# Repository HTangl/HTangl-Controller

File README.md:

# HTangl-Controller

The HTangl controller is an all digital game controller mainly made for Super Smash Brothers Melee  
but it can be used for many different games including traditional fighting games and platformers.  

It runs on a [modified version](https://github.com/HTangl/HTangl-Firmware) of the [HayB0XX firmware](https://github.com/JonnyHaystack/HayB0XX).  

The design of the controller is based on [The B0XX](https://b0xx.com/), [Frame 1](https://frame1.gg/) and [GCCMX](https://www.craneslab.xyz/projects/mx)  

This controller is not especially easy to DIY, Version 2 requiers a large 3D printed case which I print all in one piece on a large format FDM printer. The top panel and switch plate are also laser cut and the PCB requires some custom parts like the 2 USB ports. If you are not already somewhat familier with 3D printing, soldering, CAD and PCB manufacturing then I do not recommend trying to make one of these controllers.  

I created a simplified version of this controller specifically meant for DIY called the [BudgeTangl](https://github.com/HTangl/BudgeTangl), please check out that repository if you're just looking to make a simple controller.  

This controller is licensed under the CERN Open Hardware Licence Version 2 - Strongly Reciprocal. Please read the license in this repository and visit https://ohwr.org/cernohl for more information. This license allows you to make a modified or unmodified version of the controller for yourself or to sell provided you follow the guidelines of the license. The strongly reciprocal version of the license I have chosen requires that you use this same license if you decide to make modifications to any of the files in this repository.

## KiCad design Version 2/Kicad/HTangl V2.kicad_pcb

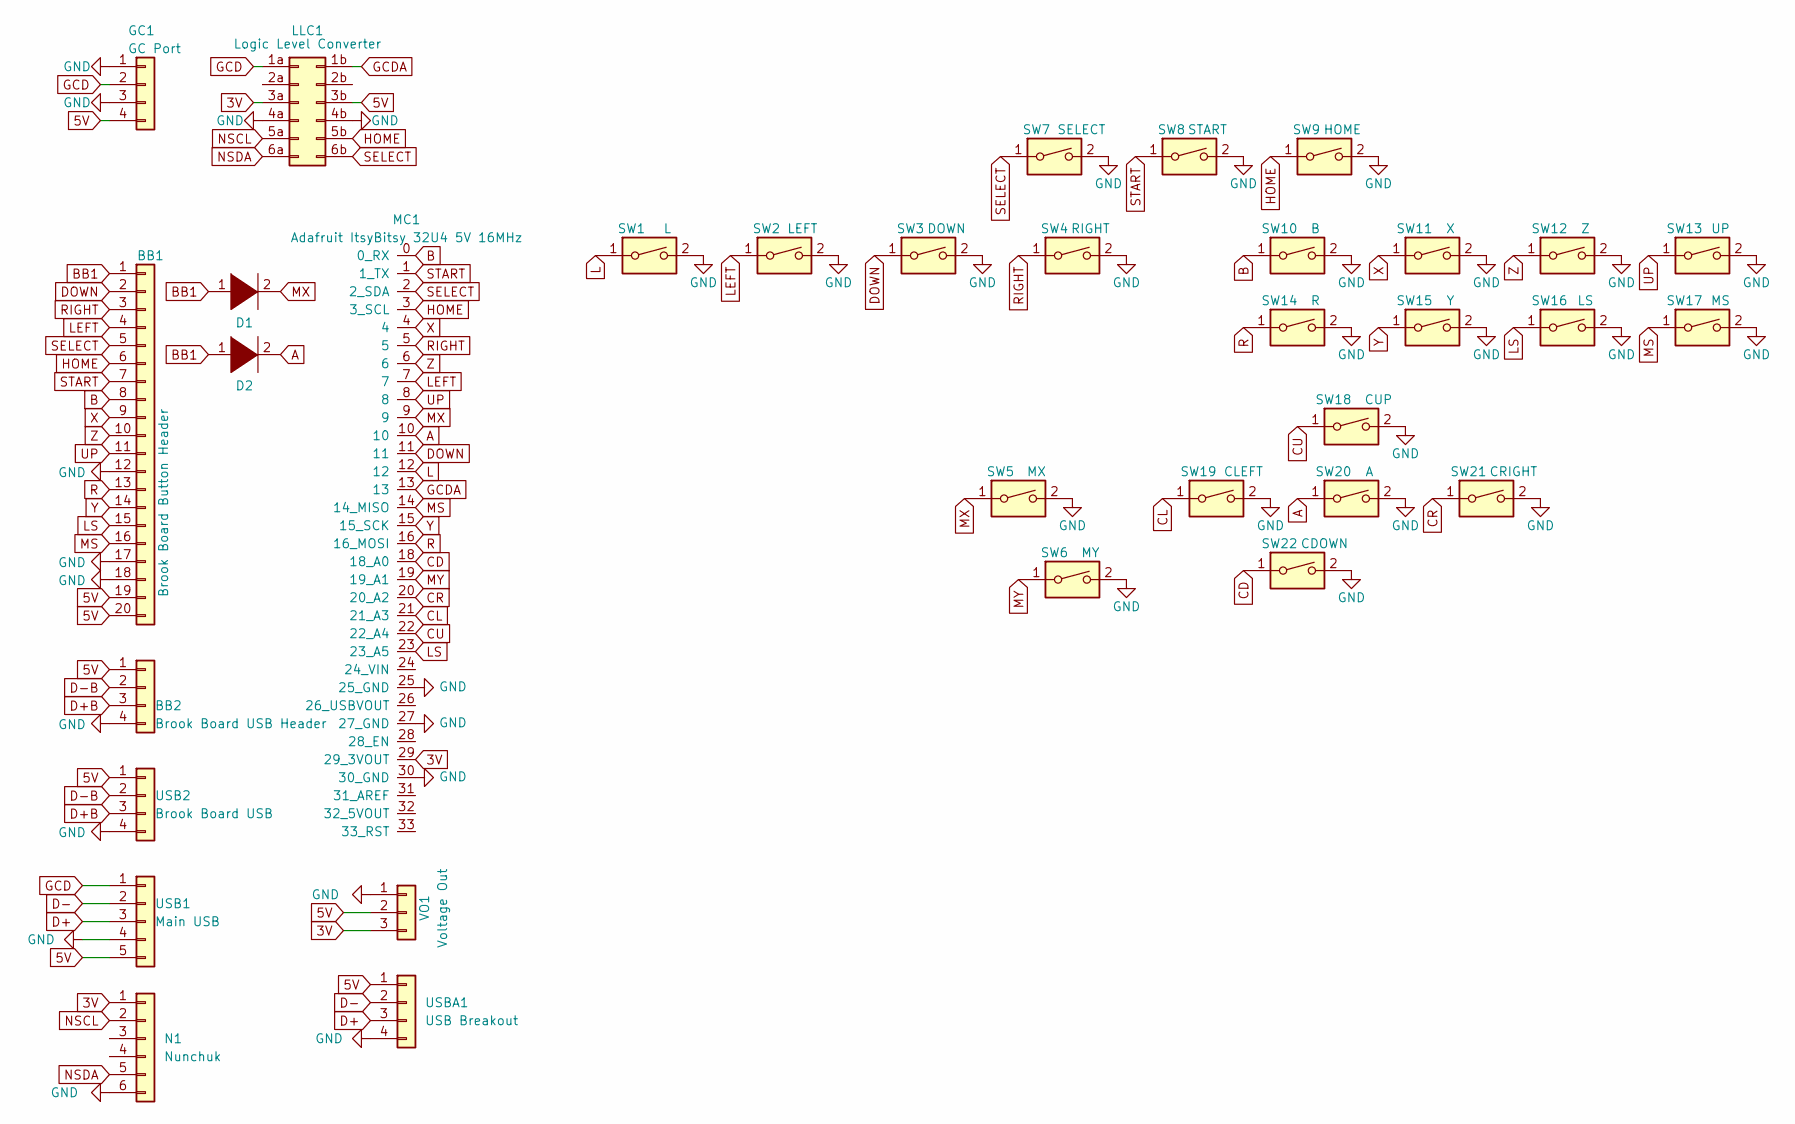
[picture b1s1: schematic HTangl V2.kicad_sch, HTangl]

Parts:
BB1: Brook Board Button Header; Brook_Board_Header_1
BB2: Brook Board USB Header; Brook_Board_Header_2
D1, D2: DIODE; D_DO-35_SOD27_P7.62mm_Horizontal
GC1: GC Port; PinSocket_1x04_P2.54mm_Vertical
LLC1: Logic Level Converter; LLC
MC1: Adafruit ItsyBitsy 32U4 5V 16MHz; Adafruit_32U4_5V
N1: Nunchuk; NunchuckFemale
SW1: L; Kailh_socket_MX_optional
SW2: LEFT; Kailh_socket_MX_optional
SW3: DOWN; Kailh_socket_MX_optional
SW4: RIGHT; Kailh_socket_MX_optional
SW5: MX; Kailh_socket_MX_optional
SW6: MY; Kailh_socket_MX_optional
SW7: SELECT; Kailh_socket_MX_optional
SW8: START; Kailh_socket_MX_optional
SW9: HOME; Kailh_socket_MX_optional
SW10: B; Kailh_socket_MX_optional
SW11: X; Kailh_socket_MX_optional
SW12: Z; Kailh_socket_MX_optional
SW13: UP; Kailh_socket_MX_optional
SW14: R; Kailh_socket_MX_optional
SW15: Y; Kailh_socket_MX_optional
SW16: LS; Kailh_socket_MX_optional
SW17: MS; Kailh_socket_MX_optional
SW18: CUP; Kailh_socket_MX_optional
SW19: CLEFT; Kailh_socket_MX_optional
SW20: A; Kailh_socket_MX_optional
SW21: CRIGHT; Kailh_socket_MX_optional
SW22: CDOWN; Kailh_socket_MX_optional
USB1: Main USB; Model_U_Header
USB2: Brook Board USB; Brook_Board_USBC
USBA1: USB Breakout; PinSocket_1x04_P2.54mm_Vertical
VO1: Voltage Out; PinHeader_1x03_P2.54mm_Vertical

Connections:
3V: LLC1.3a, MC1.29 (29_3VOUT), N1.1, VO1.3
5V: BB1.19, BB1.20, BB2.1, GC1.4, LLC1.3b, USB1.5, USB2.1, USBA1.1, VO1.2
A: D2.2 (A), MC1.10, SW20.1
B: BB1.8, MC1.0 (0_RX), SW10.1
BB1: BB1.1, D1.1 (K), D2.1 (K)
CD: MC1.18 (18_A0), SW22.1
CL: MC1.21 (21_A3), SW19.1
CR: MC1.20 (20_A2), SW21.1
CU: MC1.22 (22_A4), SW18.1
D+: USB1.3, USBA1.3
D+B: BB2.3, USB2.3
D-: USB1.2, USBA1.2
D-B: BB2.2, USB2.2
DOWN: BB1.2, MC1.11, SW3.1
GCD: GC1.2, LLC1.1a, USB1.1
GCDA: LLC1.1b, MC1.13
GND: BB1.12, BB1.17, BB1.18, BB2.4, GC1.1, GC1.3, LLC1.4a, LLC1.4b, MC1.25 (25_GND), MC1.27 (27_GND), MC1.30 (30_GND), N1.6, SW1.2, SW2.2, SW3.2, SW4.2, SW5.2, SW6.2, SW7.2, SW8.2, SW9.2, SW10.2, SW11.2, SW12.2, SW13.2, SW14.2, SW15.2, SW16.2, SW17.2, SW18.2, SW19.2, SW20.2, SW21.2, SW22.2, USB1.4, USB2.4, USBA1.4, VO1.1
HOME: BB1.6, LLC1.5b, MC1.3 (3_SCL), SW9.1
L: MC1.12, SW1.1
LEFT: BB1.4, MC1.7, SW2.1
LS: BB1.15, MC1.23 (23_A5), SW16.1
MS: BB1.16, MC1.14 (14_MISO), SW17.1
MX: D1.2 (A), MC1.9, SW5.1
MY: MC1.19 (19_A1), SW6.1
NSCL: LLC1.5a, N1.2
NSDA: LLC1.6a, N1.5
R: BB1.13, MC1.16 (16_MOSI), SW14.1
RIGHT: BB1.3, MC1.5, SW4.1
SELECT: BB1.5, LLC1.6b, MC1.2 (2_SDA), SW7.1
START: BB1.7, MC1.1 (1_TX), SW8.1
UP: BB1.11, MC1.8, SW13.1
X: BB1.9, MC1.4, SW11.1
Y: BB1.14, MC1.15 (15_SCK), SW15.1
Z: BB1.10, MC1.6, SW12.1

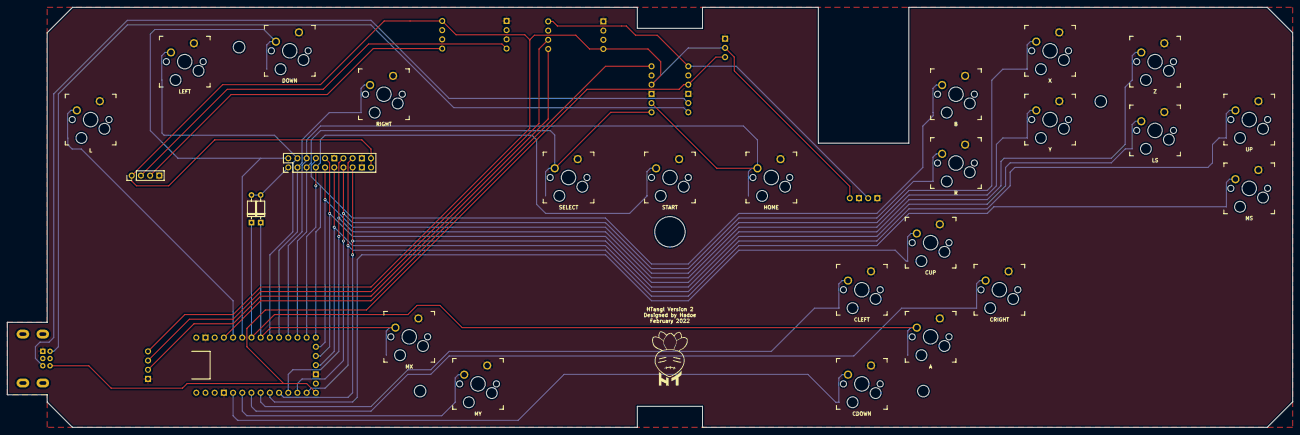
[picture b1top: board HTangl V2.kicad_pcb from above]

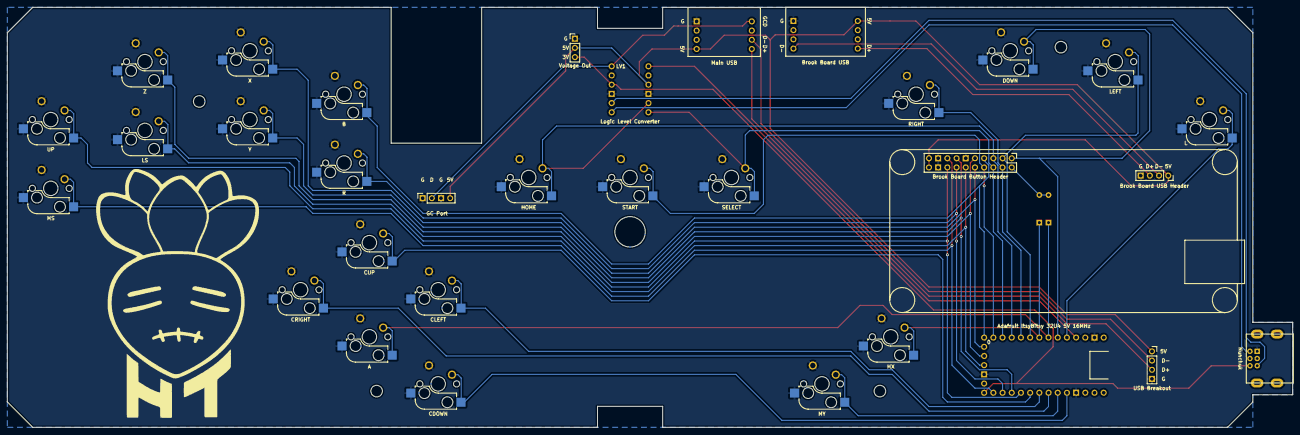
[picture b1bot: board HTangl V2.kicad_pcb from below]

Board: 2 copper layers, 355.0 x 116.0 mm, 38 parts (5 on the bottom side), 34 nets.

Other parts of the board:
., .#2, .#3, .#4: .; MountingHole_3.2mm_M3

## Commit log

2022-02-26 Update layout pics
    Updated layout pics and removed game mode pics
2022-04-09 Added V2 files
    Added Version 2 files and re organized folders
2022-04-09 Updated Pictures
2022-04-09 Add V1 Parts List
2022-04-19 Added V2 parts list
2022-04-19 Added V1 parts list
2022-04-19 Update LICENSE
    Changed license to CERN Open Hardware Licence Version 2 - Strongly Reciprocal
